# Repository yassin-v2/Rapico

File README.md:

<picture>
  <source media="(prefers-color-scheme: dark)" srcset="https://github.com/user-attachments/assets/26227bd9-6ad5-4ce1-84e2-db5a73c75b01">
  <source media="(prefers-color-scheme: light)" srcset="https://github.com/user-attachments/assets/26227bd9-6ad5-4ce1-84e2-db5a73c75b01">
  
</picture>

### A RP2040-based development board with a nRF wireless chip, designed in the Raspberry Pi Pico form factor.

----

---

## Features
- **[RP2040](https://pip-assets.raspberrypi.com/categories/814-rp2040/documents/RP-008371-DS-1-rp2040-datasheet.pdf) MCU** - 32bit dual core ARM Cortex M0+ from Raspberry Pi.
- **[nRF24L01P](https://cdn.sparkfun.com/assets/3/d/8/5/1/nRF24L01P_Product_Specification_1_0.pdf) chip** -  2.4GHz radio transceiver, with a PCB trace antenna.
- **USB C** - for programming and power.
- **Raspberry Pi Pico formfactor** - but less pins; 2x18
- **W25Q128JVPIQ flash storage chip** - 16MB high speed flash storage, intergrated with the RP2040 over quad SPI.
- **I2C and SPI** - on many pins.
- **5V and 3.3V power pins**
- Power indicator LED and another addressable LED

## Pinout

## PCB Design
*Find the PCB files [here](https://github.com/yassin-v2/Rapico/tree/main/PCB)*

The PCB is a 2 layer PCB with dimentions 51mm x 21mm.

|  |  |
|:---:|:---:|

## Schematic Design
*Find the schematic files [here](https://github.com/yassin-v2/Rapico/tree/main/PCB)*

### nRF chip schematic:

### Power input schematic:

----
|  |  |  |
|:---:|:---:|:---:|

<p align="center"><strong><em>Made with KiCad 9, as part of <a href="https://stasis.hackclub.com">Stasis</a> from <a href="https://hackclub.com/">Hackclub</a></em></strong></p>

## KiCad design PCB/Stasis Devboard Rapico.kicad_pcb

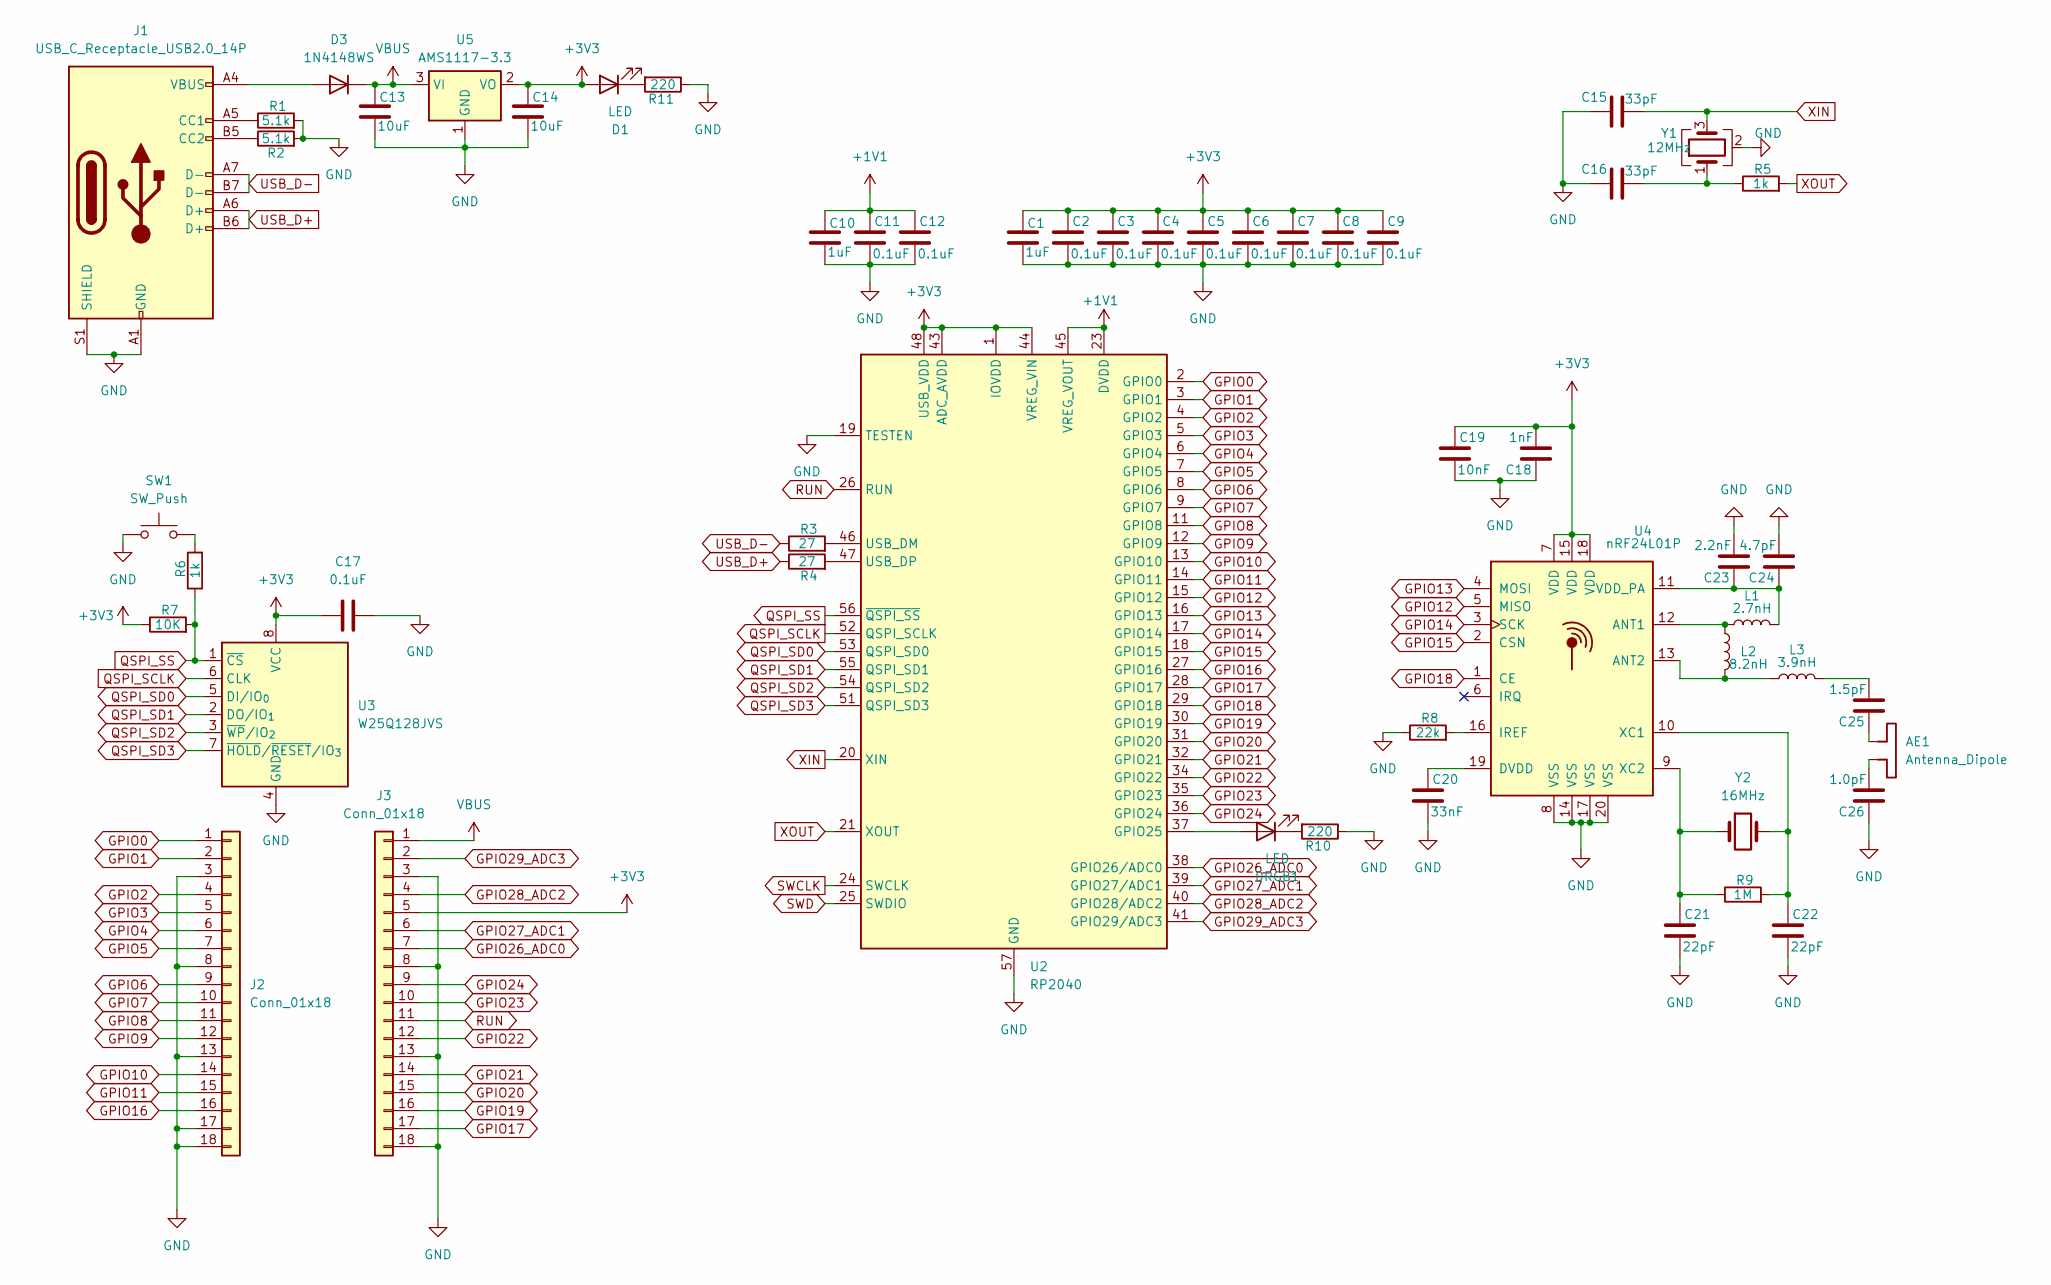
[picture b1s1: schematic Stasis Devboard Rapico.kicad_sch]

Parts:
AE1: Antenna_Dipole; Texas_SWRA117D_2.4GHz_Left
C1, C10: 1uF; C_0402_1005Metric
C2, C3, C4, C5, C6, C7, C8, C9, C11, C12, C17: 0.1uF; C_0402_1005Metric
C13: 10uF; C_0603_1608Metric
C14: 10uF; C_0402_1005Metric
C15, C16: 33pF; C_0402_1005Metric
C18: 1nF; C_0402_1005Metric
C19: 10nF; C_0402_1005Metric
C20: 33nF; C_0402_1005Metric
C21, C22: 22pF; C_0402_1005Metric
C23: 2.2nF; C_0402_1005Metric
C24: 4.7pF; C_0402_1005Metric
C25: 1.5pF; C_0402_1005Metric
C26: 1.0pF; C_0402_1005Metric
D1: LED; LED_0603_1608Metric
D3: 1N4148WS; D_SOD-323
DRGB1: LED; LED_0603_1608Metric
J1: USB_C_Receptacle_USB2.0_14P; USB_C_Receptacle_HRO_TYPE-C-31-M-12
J2, J3: Conn_01x18; PinHeader_1x18_P2.54mm_Vertical
L1: 2.7nH; L_0402_1005Metric
L2: 8.2nH; L_0402_1005Metric
L3: 3.9nH; L_0402_1005Metric
R1, R2: 5.1k; R_0402_1005Metric
R3, R4: 27; R_0402_1005Metric
R5, R6: 1k; R_0402_1005Metric
R7: 10K; R_0402_1005Metric
R8: 22k; R_0402_1005Metric
R9: 1M; R_0402_1005Metric
R10, R11: 220; R_0402_1005Metric
SW1: SW_Push; SW_TS-1088-AR02016
U2: RP2040; QFN-56-1EP_7x7mm_P0.4mm_EP3.2x3.2mm
U3: W25Q128JVS; Winbond_USON-8-1EP_3x2mm_P0.5mm_EP0.2x1.6mm
U4: nRF24L01P; QFN-20-1EP_4x4mm_P0.5mm_EP2.5x2.5mm
U5: AMS1117-3.3; SOT-89-3
Y1: 12MHz; Crystal_SMD_3225-4Pin_3.2x2.5mm
Y2: 16MHz; Crystal_SMD_3225-4Pin_3.2x2.5mm

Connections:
+1V1: C10.1, C11.1, C12.1, U2.23 (DVDD), U2.45 (VREG_VOUT), U2.50 (DVDD)
+3V3: C1.1, C2.1, C3.1, C4.1, C5.1, C6.1, C7.1, C8.1, C9.1, C14.1, C17.1, C18.2, C19.1, D1.2 (A), J3.5, R7.1, U2.1 (IOVDD), U2.10 (IOVDD), U2.22 (IOVDD), U2.33 (IOVDD), U2.42 (IOVDD), U2.43 (ADC_AVDD), U2.44 (VREG_VIN), U2.48 (USB_VDD), U2.49 (IOVDD), U3.8 (VCC), U4.7 (VDD), U4.15 (VDD), U4.18 (VDD), U5.2 (VO)
GPIO0: J2.1, U2.2 (GPIO0)
GPIO1: J2.2, U2.3 (GPIO1)
GPIO2: J2.4, U2.4 (GPIO2)
GPIO3: J2.5, U2.5 (GPIO3)
GPIO4: J2.6, U2.6 (GPIO4)
GPIO5: J2.7, U2.7 (GPIO5)
GPIO6: J2.9, U2.8 (GPIO6)
GPIO7: J2.10, U2.9 (GPIO7)
GPIO8: J2.11, U2.11 (GPIO8)
GPIO9: J2.12, U2.12 (GPIO9)
GPIO10: J2.14, U2.13 (GPIO10)
GPIO11: J2.15, U2.14 (GPIO11)
GPIO12: U2.15 (GPIO12), U4.5 (MISO)
GPIO13: U2.16 (GPIO13), U4.4 (MOSI)
GPIO14: U2.17 (GPIO14), U4.3 (SCK)
GPIO15: U2.18 (GPIO15), U4.2 (CSN)
GPIO16: J2.16, U2.27 (GPIO16)
GPIO17: J3.17, U2.28 (GPIO17)
GPIO18: U2.29 (GPIO18), U4.1 (CE)
GPIO19: J3.16, U2.30 (GPIO19)
GPIO20: J3.15, U2.31 (GPIO20)
GPIO21: J3.14, U2.32 (GPIO21)
GPIO22: J3.12, U2.34 (GPIO22)
GPIO23: J3.10, U2.35 (GPIO23)
GPIO24: J3.9, U2.36 (GPIO24)
GPIO26_ADC0: J3.7, U2.38 (GPIO26/ADC0)
GPIO27_ADC1: J3.6, U2.39 (GPIO27/ADC1)
GPIO28_ADC2: J3.4, U2.40 (GPIO28/ADC2)
GPIO29_ADC3: J3.2, U2.41 (GPIO29/ADC3)
unnamed: AE1.1, C25.1
unnamed: AE1.2, C26.2
unnamed: C16.2, R5.1, Y1.1
unnamed: C25.2, L3.2
unnamed: D1.1 (K), R11.2
unnamed: D3.2 (A), J1.A4 (VBUS), J1.A9 (VBUS), J1.B4 (VBUS), J1.B9 (VBUS)
unnamed: DRGB1.2 (A), U2.37 (GPIO25)
unnamed: DRGB1.1 (K), R10.2
unnamed: J1.A5 (CC1), R1.1
unnamed: J1.B5 (CC2), R2.1
unnamed: R6.2, SW1.2
unnamed: R3.2, U2.46 (USB_DM)
unnamed: R4.2, U2.47 (USB_DP)
unnamed: L1.1, L2.1, U4.12 (ANT1)
unnamed: L2.2, L3.1, U4.13 (ANT2)
unnamed: C20.1, U4.19 (DVDD)
unnamed: R8.2, U4.16 (IREF)
unnamed: C23.1, C24.1, L1.2, U4.11 (VDD_PA)
unnamed: C21.1, R9.1, U4.9 (XC2), Y2.1
QSPI_SCLK: U2.52 (QSPI_SCLK), U3.6 (CLK)
QSPI_SD0: U2.53 (QSPI_SD0), U3.5 (DI/IO_{0})
QSPI_SD1: U2.55 (QSPI_SD1), U3.2 (DO/IO_{1})
QSPI_SD2: U2.54 (QSPI_SD2), U3.3 (~WP/IO_{2})
QSPI_SD3: U2.51 (QSPI_SD3), U3.7 (~HOLD/~RESET/IO_{3})
QSPI_SS: R6.1, R7.2, U2.56 (~QSPI_SS), U3.1 (~CS)
RUN: J3.11, U2.26 (RUN)
SWCLK: U2.24 (SWCLK)
SWD: U2.25 (SWDIO)
USB_D+: J1.A6 (D+), J1.B6 (D+), R4.1
USB_D-: J1.A7 (D-), J1.B7 (D-), R3.1
VBUS: C13.1, D3.1 (K), J3.1, U5.3 (VI)
XIN: C15.2, U2.20 (XIN), Y1.3
XOUT: R5.2, U2.21 (XOUT)

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
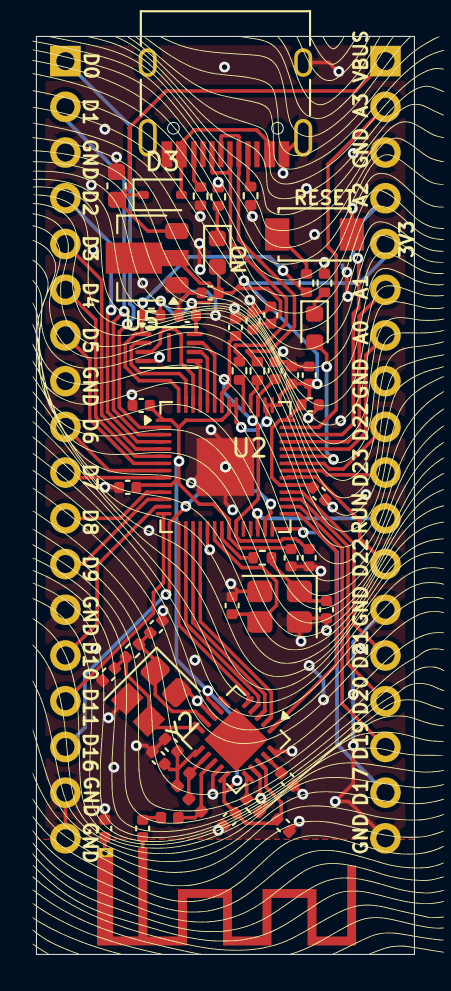
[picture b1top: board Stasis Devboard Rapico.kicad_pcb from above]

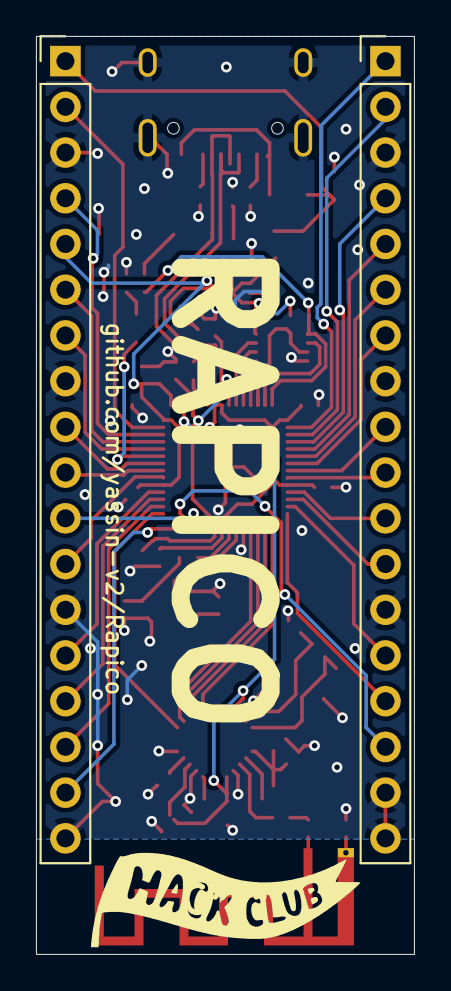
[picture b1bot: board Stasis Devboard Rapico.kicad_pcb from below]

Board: 2 copper layers, 21.0 x 51.0 mm, 54 parts (2 on the bottom side), 64 nets.

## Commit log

2026-04-13 Rename project from 'Rapico' to 'The Rapico'
2026-04-21 Adding PCB and images
2026-04-21 Added images and features
    Updated the README to include image and, features
2026-04-21 Fixed PNG Logo
    Fixed PNG logo.
2026-04-21 Higher res PCB images
2026-04-21 Added board pinout image
2026-04-21 Board pinout v2
2026-04-21 Pinout AGAIN
2026-04-21 V4 pinout
2026-04-21 Added .step file
2026-04-22 Create LICENSE
2026-05-05 Picture of rapico
2026-05-05 Update README with additional image
